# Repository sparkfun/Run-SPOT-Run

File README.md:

SatUpLink Shield
================
[  
*SatUpLink Shield(DEV-11088)*](https://www.sparkfun.com/products/11088)

Run SPOT Run is a breakout board for the SPOT Connect version of the SPOT Geolocator. It is now retired on the SparkFun store front.

You will need your own registered SPOT ($150 for the hardware, $100 for the subscription), but after that, you should be able to broadcast small text messages (up to 40 characters) from most land masses on the globe.

Please see this [tutorial](http://www.sparkfun.com/tutorials/340) for more information. 

The hardware files were designed in Eagle v6.1.0 , and the firmware was developed in Arduino v1.0.

Repository Contents
-------------------
* **/Firmware** - Example Arduino sketch for running the shield 
* **/Hardware** - All Eagle design files (.brd, .sch)

License Information
-------------------
The hardware is released under [Creative Commons Share-alike 3.0](http://creativecommons.org/licenses/by-sa/3.0/).  
All other code is open source so please feel free to do anything you want with it; you buy me a beer if you use this and we meet someday ([Beerware license](http://en.wikipedia.org/wiki/Beerware)).

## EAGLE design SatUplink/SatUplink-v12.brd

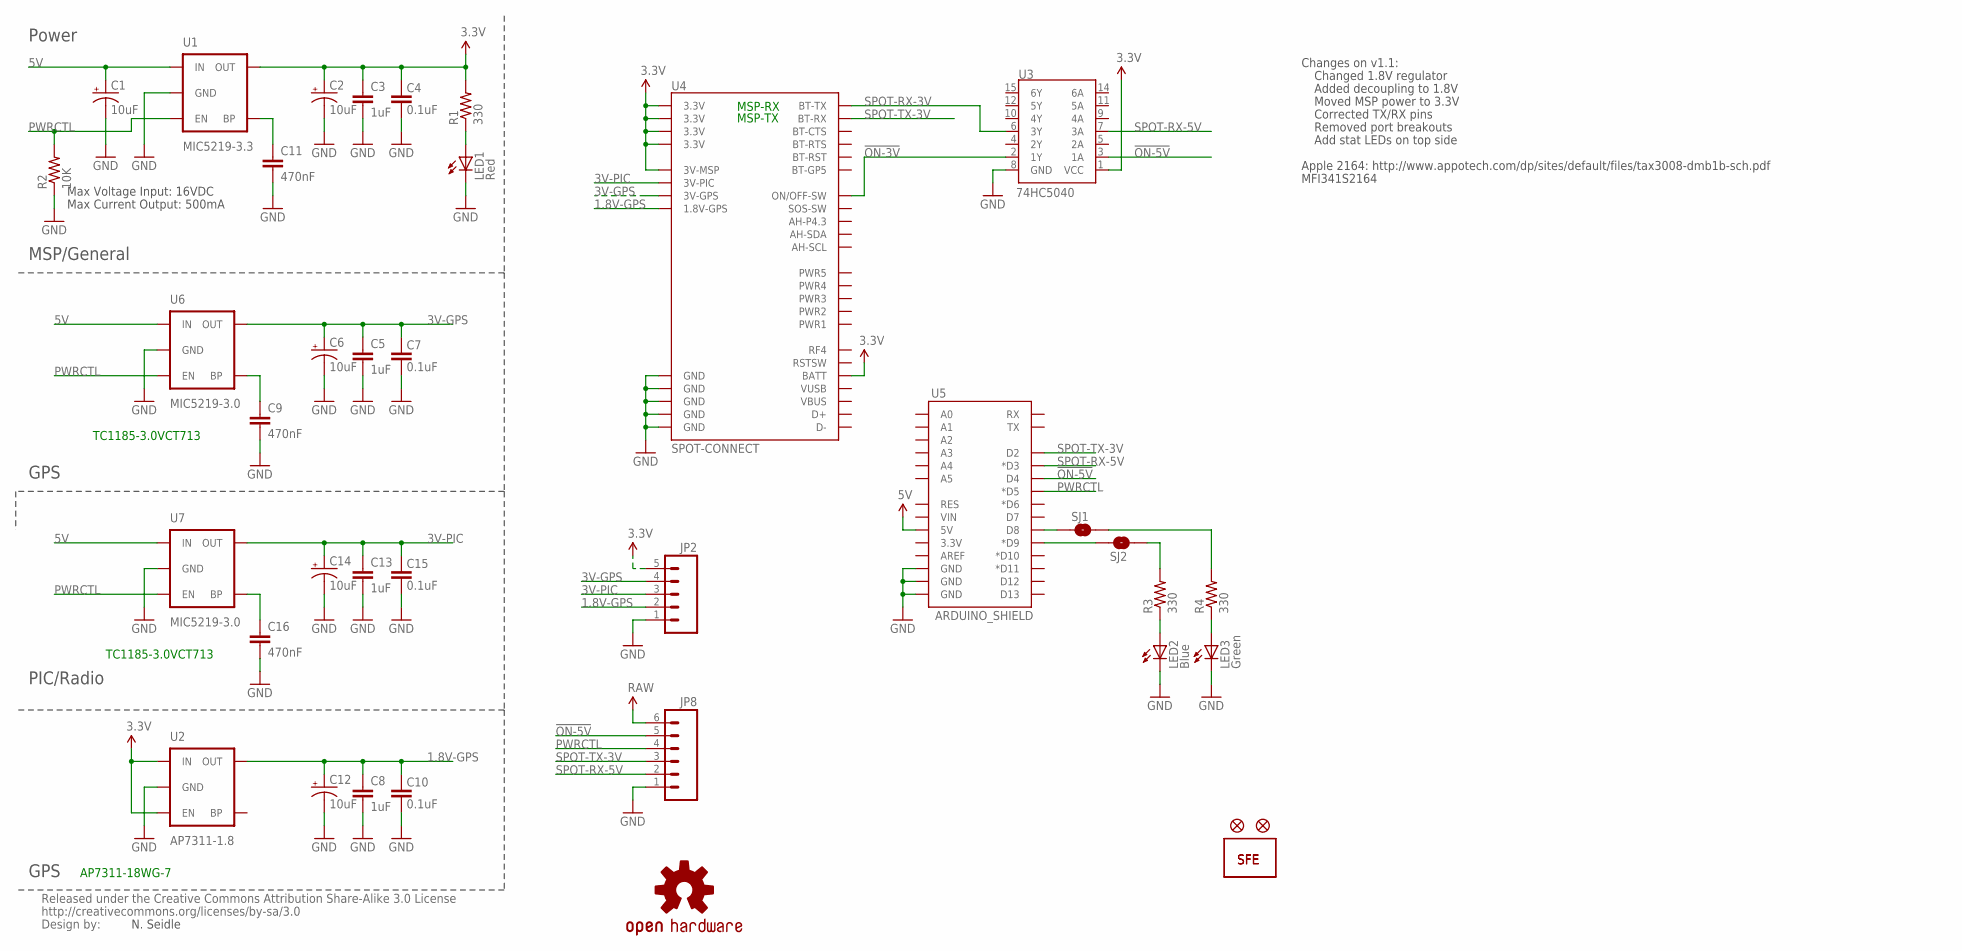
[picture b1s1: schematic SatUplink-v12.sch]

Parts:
C1, C2, C6, C12, C14: 10uF; EIA3216
C3, C5, C8, C13: 1uF; 0402-CAP
C4, C7, C10, C15: 0.1uF; 0402-CAP
C9, C11, C16: 470nF; 0402-CAP
JP2: M05PTH; 1X05
JP8: M06SIP; 1X06
JP10, JP11: FIDUCIALUFIDUCIAL; MICRO-FIDUCIAL
LED1: Red; LED-0603
LED2: Blue; LED-0603
LED3: Green; LED-0603
R1, R3, R4: 330; 0402-RES
R2: 10K; 0402-RES
SJ1, SJ2: SOLDERJUMPERTRACE; SJ_2S-TRACE
U1: MIC5219-3.3; SOT23-5
U2: AP7311-1.8; SOT23-5
U3: 74HC5040; SO016
U4: SPOT-CONNECT
U5: ARDUINO_SHIELD; DUEMILANOVE_VIAS
U6, U7: MIC5219-3.0; SOT23-5
U$1: LOGO-SFESK; SFE-LOGO-FLAME
U$2: CREATIVE_COMMONS
U$3: OSHW-LOGOS; OSHW-LOGO-S
U$11: LOGO-SFENEW; SFE-NEW-WEBLOGO

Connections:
1.8V-GPS: C8.1, C10.2, C12.A (+), JP2.2, U2.5 (OUT), U4.1.8V-GPS
3.3V: C2.A (+), C3.1, C4.2, JP2.5, R1.2, U1.5 (OUT), U2.1 (IN), U2.3 (EN), U3.1 (VCC), U4.3.3V@1 (3.3V), U4.3.3V@2 (3.3V), U4.3.3V@3 (3.3V), U4.3.3V@4 (3.3V), U4.3VMSP (3V-MSP), U4.BATT
3V-GPS: C5.1, C6.A (+), C7.2, JP2.4, U4.3V-GPS, U6.5 (OUT)
3V-PIC: C13.1, C14.A (+), C15.2, JP2.3, U4.3VPIC (3V-PIC), U7.5 (OUT)
5V: C1.A (+), JP8.6, U1.1 (IN), U5.5V, U6.1 (IN), U7.1 (IN)
!ON-3V: U3.2 (1Y), U4.ON/OFF (ON/OFF-SW)
!ON-5V: JP8.5, U3.3 (1A), U5.D4
GND: C1.C (-), C2.C (-), C3.2, C4.1, C5.2, C6.C (-), C7.1, C8.2, C9.2, C10.1, C11.2, C12.C (-), C13.2, C14.C (-), C15.1, C16.2, JP2.1, JP8.1, LED1.C, LED2.C, LED3.C, R2.1, U1.2 (GND), U2.2 (GND), U3.8 (GND), U4.GND@1 (GND), U4.GND@2 (GND), U4.GND@3 (GND), U4.GND@4 (GND), U4.GND@5 (GND), U5.GND@0 (GND), U5.GND@1 (GND), U5.GND@2 (GND), U6.2 (GND), U7.2 (GND)
unnamed: C16.1, U7.4 (BP)
unnamed: R4.2, SJ1.2
unnamed: R3.2, SJ2.2
unnamed: C9.1, U6.4 (BP)
unnamed: LED2.A, R3.1
unnamed: LED3.A, R4.1
unnamed: SJ1.1, U5.D8
unnamed: SJ2.1, U5.D9 (*D9)
unnamed: C11.1, U1.4 (BP)
unnamed: LED1.A, R1.1
PWRCTL: JP8.4, R2.2, U1.3 (EN), U5.D5 (*D5), U6.3 (EN), U7.3 (EN)
SPOT-RX-3V: U3.6 (3Y), U4.BT-TX
SPOT-RX-5V: JP8.2, U3.7 (3A), U5.D3 (*D3)
SPOT-TX-3V: JP8.3, U4.BT-RX, U5.D2

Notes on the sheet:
Max Voltage Input: 16VDC
Max Current Output: 500mA
N. Seidle
TC1185-3.0VCT713
Add stat LEDs on top side
Apple 2164: http://www.appotech.com/dp/sites/default/files/tax3008-dmb1b-sch.pdf
MFI341S2164
MSP-TX
MSP-RX
AP7311-18WG-7
Changes on v1.1:
Added decoupling to 1.8V
Changed 1.8V regulator
Moved MSP power to 3.3V
Corrected TX/RX pins
Removed port breakouts
PIC/Radio
GPS
MSP/General
Power

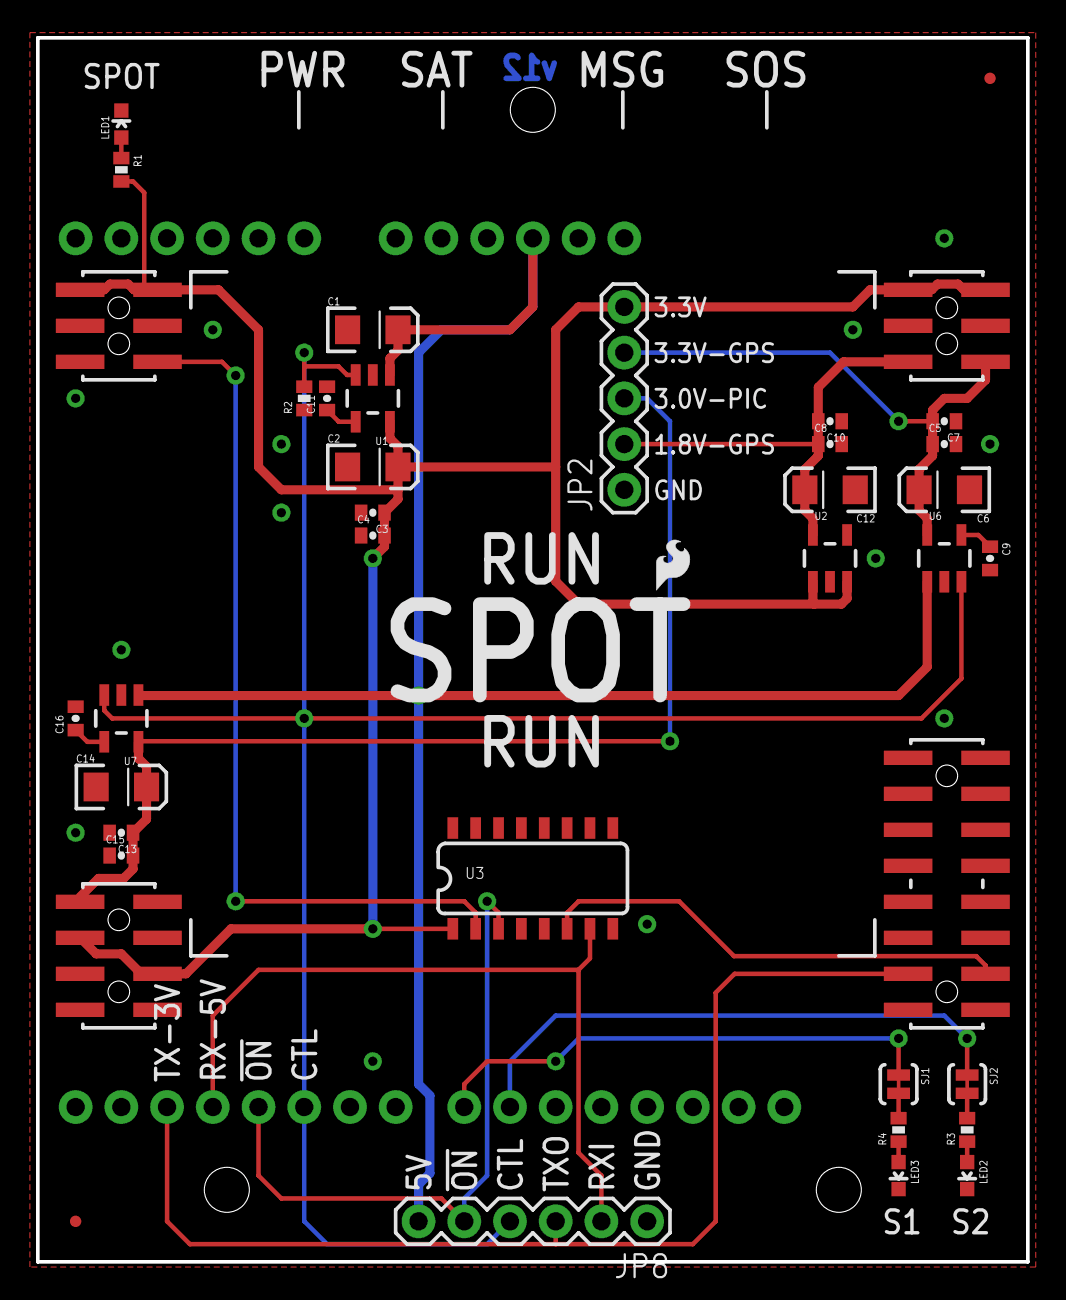
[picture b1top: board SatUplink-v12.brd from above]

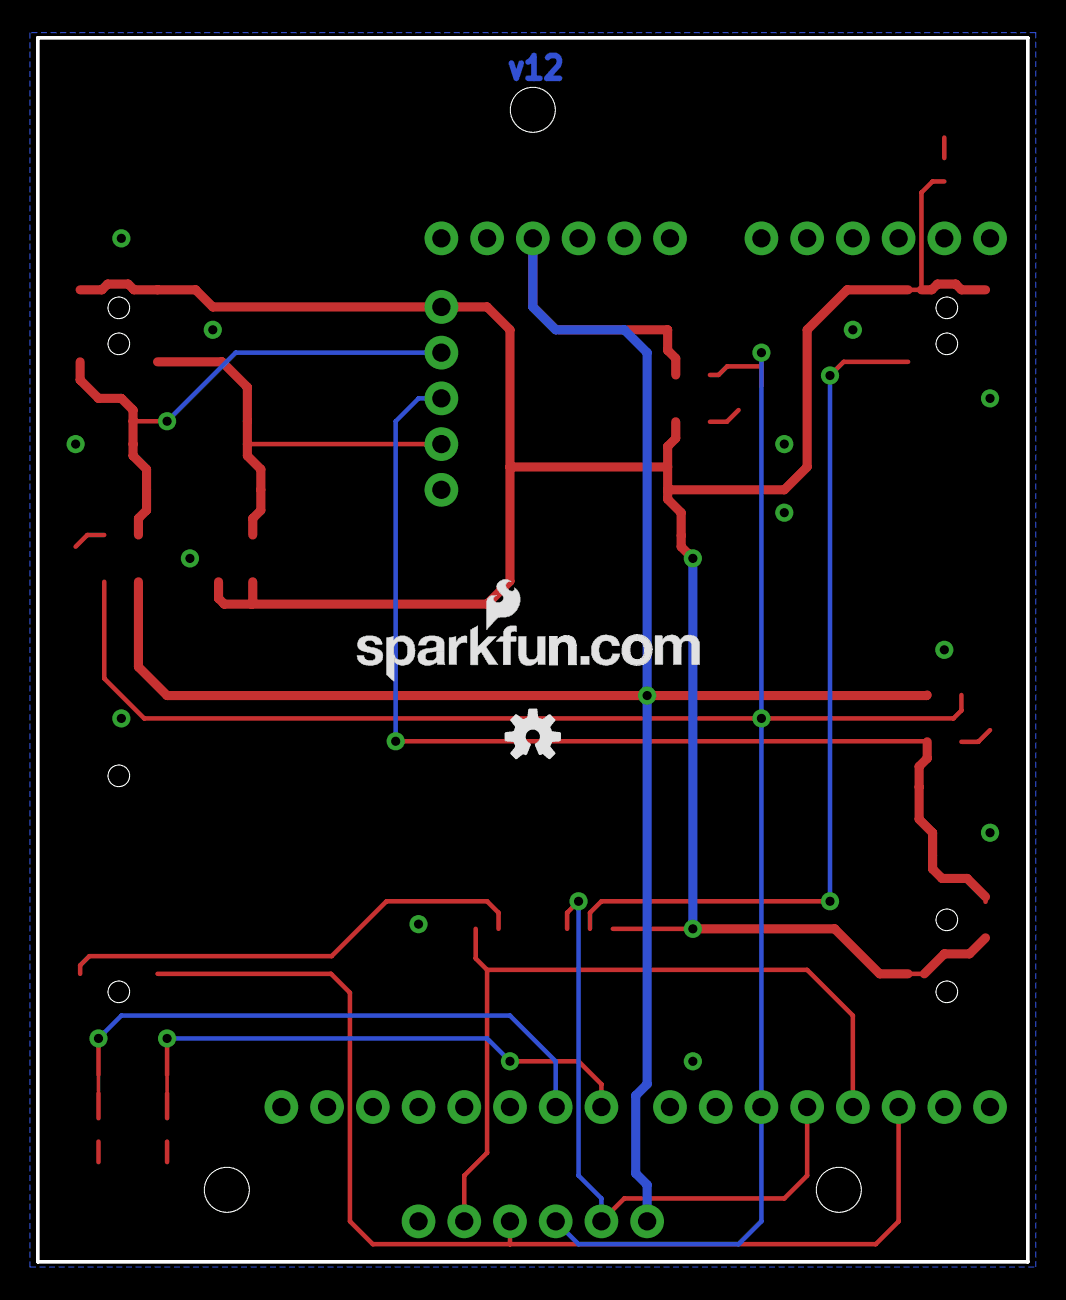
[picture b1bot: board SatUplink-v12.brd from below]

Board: 2 copper layers, 55.0 x 68.0 mm, 40 parts (2 on the bottom side), 22 nets.

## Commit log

2012-04-03 Original commit.
2012-04-03 Adding readme info.
2012-04-10 Fixing schematic typo.
2013-04-18 Fix repo structure, add .git files, update README
2013-04-18 Update README.md
    Added in Eagle version number.

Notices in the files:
parts and their libraries:
SparkFun: Released under the Creative Commons Attribution Share-Alike 3.0 License
